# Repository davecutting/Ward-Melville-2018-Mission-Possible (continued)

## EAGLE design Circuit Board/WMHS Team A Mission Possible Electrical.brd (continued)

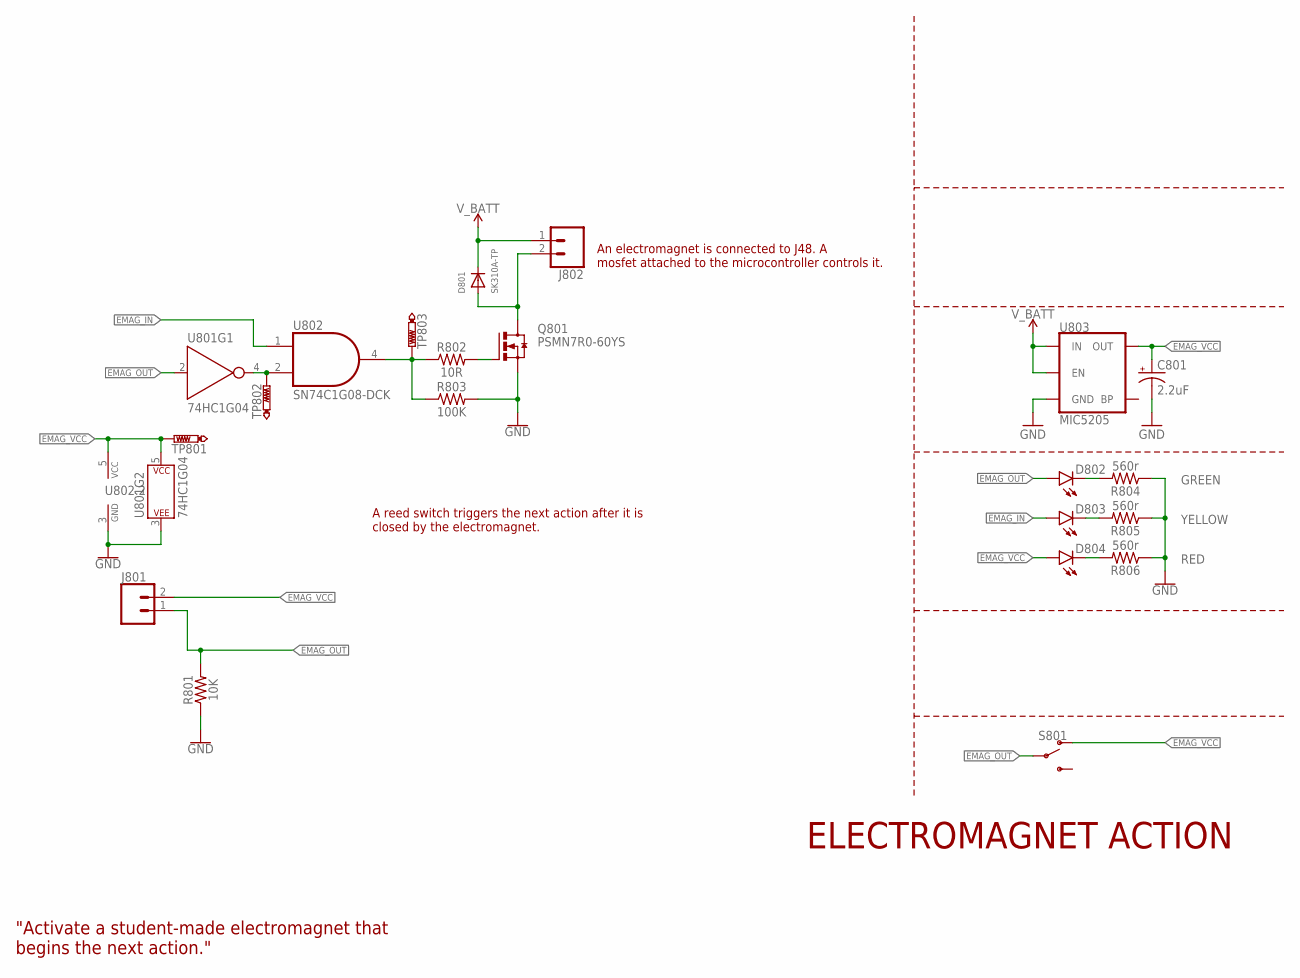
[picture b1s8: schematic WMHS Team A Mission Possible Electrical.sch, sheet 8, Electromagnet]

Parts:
C801: 2.2uF; EIA3216
D801: SK310A-TP; SMADIODE
D802: GREEN; LED-0603
D803: YELLOW; LED-0603
D804: RED; LED-0603
J801: CONN_02LOCK; 1X02_LOCK
J802: CONN_023.5MM_LOCK; SCREWTERMINAL-3.5MM-2_LOCK
Q801: PSMN7R0-60YS; SOT669
R801: 10K; 0603
R802: 10R; 0603
R803: 100K; 0603
R804, R805, R806: 560r; 0603
S801: SWITCH-SPDT-SMD-AYZ0202; SWITCH_DPDT_SMD_AYZ0202
TP801, TP802, TP803: PTR1TP20R; TP20R
U801: 74HC1G04; SOT353
U802: SN74C1G08-DCK; SC-70-5
U803: MIC5205; SOT23-5

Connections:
EMAG_IN: D803.A, U802.1 (A); also elsewhere on the board
EMAG_OUT: D802.A, J801.1, R801.2, S801.2, U801.2 (A); also elsewhere on the board
EMAG_VCC: C801.+, D804.A, J801.2, S801.1 (O), TP801.TP, U801.5 (P$V+), U802.5 (VCC), U803.5 (OUT)
GND: C801.-, Q801.1 (S), Q801.2 (S), Q801.3 (S), R801.1, R803.2, R804.1, R805.1, R806.1, U801.3 (P$V-), U802.3 (GND), U803.2 (GND); also elsewhere on the board
unnamed: TP802.TP, U801.4 (Y), U802.2 (B)
unnamed: R802.1, R803.1, TP803.TP, U802.4 (Y)
unnamed: Q801.4 (G), R802.2
unnamed: D801.A, J802.2, Q801.MB (D)
unnamed: D804.C, R806.2
unnamed: D803.C, R805.2
unnamed: D802.C, R804.2
V_BATT: D801.C, J802.1, U803.1 (IN), U803.3 (EN); also elsewhere on the board

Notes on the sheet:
ELECTROMAGNET ACTION
"Activate a student-made electromagnet that begins the next action."
An electromagnet is connected to J48. A mosfet attached to the microcontroller controls it.
A reed switch triggers the next action after it is closed by the electromagnet.

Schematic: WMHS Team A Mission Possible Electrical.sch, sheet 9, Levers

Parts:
C901: 0.1uF; 0603
C902: 2.2uF; EIA3216
D901: SK310A-TP; SMADIODE
D902: GREEN; LED-0603
D903: YELLOW; LED-0603
D904: RED; LED-0603
J901: CONN_02LOCK; 1X02_LOCK
J902: CONN_023.5MM_LOCK; SCREWTERMINAL-3.5MM-2_LOCK
J903: ICSP_HEADER; 2X3
Q901: PSMN7R0-60YS; SOT669
R901: 10R; 0603
R902: 100K; 0603
R903, R904: 10K; 0603
R905, R906, R907: 560r; 0603
S901: RST; TACTILE_SWITCH_SMD_5.2MM
S902: SWITCH-SPDT-SMD-AYZ0202; SWITCH_DPDT_SMD_AYZ0202
TP901, TP902: PTR1TP20R; TP20R
U901: ATTINY25-20SSUR; SOIC8
U902: MIC5205; SOT23-5

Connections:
GND: C901.1, C902.-, J903.6, Q901.1 (S), Q901.2 (S), Q901.3 (S), R902.2, R903.2, R905.1, R906.1, R907.1, S901.1, S901.2 (1), U901.4 (GND), U902.2 (GND); also elsewhere on the board
LEVER_IN: D903.A, U901.2 (PB3(ADC3)); also elsewhere on the board
LEVER_MISO: J903.1, U901.6 (PB1(MISO))
LEVER_MOSI: J903.4, U901.5 (PB0(MOSI))
LEVER_OUT: D902.A, J901.2, R903.1, S902.2; also elsewhere on the board
LEVER_RST: J903.5, R904.1, S901.3 (2), S901.4 (2), U901.1 (PB5(NRES))
LEVER_SCK: J903.3, R901.1, R902.1, U901.7 (PB2(SCK/ADC1))
LEVER_VCC: C901.2, C902.+, D904.A, J901.1, J903.2, R904.2, S902.1 (O), TP901.TP, U901.8 (VCC), U902.5 (OUT)
unnamed: TP902.TP, U901.3 (PB4(ADC2))
unnamed: Q901.4 (G), R901.2
unnamed: D901.A, J902.2, Q901.MB (D)
unnamed: D904.C, R907.2
unnamed: D903.C, R906.2
unnamed: D902.C, R905.2
V_BATT: D901.C, J902.1, U902.1 (IN), U902.3 (EN); also elsewhere on the board

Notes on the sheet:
LEVER ACTION
"Use the mechanical advantage of all 3 classes of levers in sequence to begin the next action."
A solenoid is connected to J50. A mosfet attached to the microcontroller controls it. After a short period of activation, the mosfet is turned off and the solenoid releases.
A normally open limit switch connected to J53 is pressed by the levers.
https://www.ebay.com/itm/DC12V-2A-20N-10mm-Pull-Push-Type-Linear-Motion-Solenoid-Electromagnet-/ 253056280056?_trksid=p2349526.m4383.l4275.c1

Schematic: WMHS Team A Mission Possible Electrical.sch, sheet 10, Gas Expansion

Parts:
C1001: 0.1uF; 0603
C1002: 2.2uF; EIA3216
D1001: SK310A-TP; SMADIODE
D1002: GREEN; LED-0603
D1003: YELLOW; LED-0603
D1004: RED; LED-0603
J1001: CONN_023.5MM_LOCK; SCREWTERMINAL-3.5MM-2_LOCK
J1002, J1003, J1004: CONN_02LOCK; 1X02_LOCK
J1005: ICSP_HEADER; 2X3
Q1001: PSMN7R0-60YS; SOT669
R1001: 10R; 0603
R1002, R1003: 100K; 0603
R1004: 1M; 0603
R1005: 10K; 0603
R1006, R1007, R1008: 560r; 0603
S1001: RST; TACTILE_SWITCH_SMD_5.2MM
S1002: SWITCH-SPDT-SMD-AYZ0202; SWITCH_DPDT_SMD_AYZ0202
TP1001, TP1002: PTR1TP20R; TP20R
U1001: ATTINY25-20SSUR; SOIC8
U1002: MIC5205; SOT23-5

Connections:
EXP_IN: D1003.A, U1001.2 (PB3(ADC3)); also elsewhere on the board
EXP_MISO: J1005.1, U1001.6 (PB1(MISO))
EXP_MOSI: J1005.4, R1001.1, R1002.1, U1001.5 (PB0(MOSI))
EXP_OUT: D1002.A, J1004.2, R1004.1, S1002.2; also elsewhere on the board
EXP_RST: J1005.5, R1005.1, S1001.3 (2), S1001.4 (2), U1001.1 (PB5(NRES))
EXP_SCK: J1005.3, R1003.2, U1001.7 (PB2(SCK/ADC1))
EXP_VCC: C1001.2, C1002.+, D1004.A, J1004.1, J1005.2, R1005.2, S1002.1 (O), TP1001.TP, U1001.8 (VCC), U1002.5 (OUT)
GND: C1001.1, C1002.-, J1002.2, J1003.2, J1005.6, Q1001.1 (S), Q1001.2 (S), Q1001.3 (S), R1002.2, R1004.2, R1006.1, R1007.1, R1008.1, S1001.1, S1001.2 (1), U1001.4 (GND), U1002.2 (GND); also elsewhere on the board
unnamed: Q1001.4 (G), R1001.2
unnamed: TP1002.TP, U1001.3 (PB4(ADC2))
unnamed: J1002.1, R1003.1
unnamed: D1001.A, J1001.2, Q1001.MB (D)
unnamed: D1004.C, R1008.2
unnamed: D1003.C, R1007.2
unnamed: D1002.C, R1006.2
V_BATT: D1001.C, J1001.1, J1003.1, U1002.1 (IN), U1002.3 (EN); also elsewhere on the board

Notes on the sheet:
GAS EXPANSION ACTION
"Use a thermal reaction which expands a gas to activate the next action." CLARIFICATION: "Use a change in temperature which expands a gas to activate the next action."
12V 40W ceramic cartridge heater is connected to J38. A mosfet attached to the microcontroller controls the heater.
A normally open limit switch connected to J1 is pressed by the expanding gas pushing on and displacing the syringe plunger.
A thermistor connected to J39 provides feedback for the heater cartridge and is used in the PID loop.
An optional 12V brushless fan can be connected to J5 in order to cool the interface between the heater and the device

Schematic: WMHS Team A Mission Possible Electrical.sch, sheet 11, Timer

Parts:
C1101, C1103: 0.1uF; 0603
C1102: 0.33uF; 0603
D1101: GREEN; LED-0603
D1102: YELLOW; LED-0603
D1103: RED; LED-0603
IC1101: 7805DT; TO252
J1101, J1102, J1103: CONN_02LOCK; 1X02_LOCK
J1104: ICSP_HEADER; 2X3
R1101, R1102, R1103: 10K; 0603
R1104, R1105, R1106: 560r; 0603
S1101: RST; TACTILE_SWITCH_SMD_5.2MM
S1102: SWITCH-SPDT-SMD-AYZ0202; SWITCH_DPDT_SMD_AYZ0202
TP1101, TP1102: PTR1TP20R; TP20R
U1101: DRV8835; WSON-12
U1102: ATTINY25-20SSUR; SOIC8

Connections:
GND: C1101.1, C1102.1, C1103.2, IC1101.3 (GND), J1104.6, R1101.2, R1102.2, R1104.1, R1105.1, R1106.1, S1101.1, S1101.2 (1), U1101.6 (VSS), U1101.PAD (VSS), U1102.4 (GND); also elsewhere on the board
unnamed: TP1102.TP, U1102.3 (PB4(ADC2))
unnamed: J1102.1, U1101.2 (AOUT1)
unnamed: J1102.2, U1101.3 (AOUT2)
unnamed: D1103.C, R1106.2
unnamed: D1102.C, R1105.2
unnamed: D1101.C, R1104.2
TIMER_IN: D1102.A, U1102.2 (PB3(ADC3)); also elsewhere on the board
TIMER_MISO: J1104.1, U1101.9 (AIN2/EN), U1102.6 (PB1(MISO))
TIMER_MOSI: J1104.4, U1101.10 (AIN1/PH), U1102.5 (PB0(MOSI))
TIMER_OUT: D1101.A, J1101.2, R1101.1, S1102.2; also elsewhere on the board
TIMER_RST: J1104.5, R1103.1, S1101.3 (2), S1101.4 (2), U1102.1 (PB5(NRES))
TIMER_SCK: J1103.2, J1104.3, R1102.1, U1102.7 (PB2(SCK/ADC1))
TIMER_VCC: C1101.2, C1103.1, D1103.A, IC1101.2 (VO), J1101.1, J1103.1, J1104.2, R1103.2, S1102.1 (O), TP1101.TP, U1101.1 (VM), U1101.11 (MODE), U1101.12 (VCC), U1102.8 (VCC)
V_BATT: C1102.2, IC1101.1 (VI); also elsewhere on the board

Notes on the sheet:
CHEMICAL TIMER
"To receive Bonus Points, participants must designate an action, either scorable or non- scorable, taking over 30 seconds that does not use electricity or springs for power."
A normally open limit switch connected to J55 is pressed by the expanding gas.
A motor connected to J54 flips the pressure chamber then pulses back and forth for several seconds to ensure the alkaseltzer is mixing with the water.
A normally open limit switch tells the motor driver when to shut off.

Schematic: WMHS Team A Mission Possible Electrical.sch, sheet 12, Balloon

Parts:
C1201, C1203: 0.1uF; 0603
C1202: 0.33uF; 0603
D1201: GREEN; LED-0603
D1202: YELLOW; LED-0603
D1203: RED; LED-0603
IC1201: 7805DT; TO252
J1201, J1202, J1203: CONN_02LOCK; 1X02_LOCK
J1204: ICSP_HEADER; 2X3
R1201, R1202, R1203: 10K; 0603
R1204, R1205, R1206: 560r; 0603
S1201: RST; TACTILE_SWITCH_SMD_5.2MM
S1202: SWITCH-SPDT-SMD-AYZ0202; SWITCH_DPDT_SMD_AYZ0202
TP1201, TP1202: PTR1TP20R; TP20R
U1201: DRV8835; WSON-12
U1202: ATTINY25-20SSUR; SOIC8

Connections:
BALLOON_IN: D1202.A, U1202.2 (PB3(ADC3)); also elsewhere on the board
BALLOON_MISO: J1204.1, U1201.9 (AIN2/EN), U1202.6 (PB1(MISO))
BALLOON_MOSI: J1204.4, U1201.10 (AIN1/PH), U1202.5 (PB0(MOSI))
BALLOON_OUT: D1201.A, J1201.2, R1201.1, S1202.2; also elsewhere on the board
BALLOON_RST: J1204.5, R1203.1, S1201.3 (2), S1201.4 (2), U1202.1 (PB5(NRES))
BALLOON_SCK: J1202.2, J1204.3, R1202.1, U1202.7 (PB2(SCK/ADC1))
BALLOON_VCC: C1201.2, C1203.1, D1203.A, IC1201.2 (VO), J1201.1, J1202.1, J1204.2, R1203.2, S1202.1 (O), TP1201.TP, U1201.1 (VM), U1201.11 (MODE), U1201.12 (VCC), U1202.8 (VCC)
GND: C1201.1, C1202.1, C1203.2, IC1201.3 (GND), J1204.6, R1201.2, R1202.2, R1204.1, R1205.1, R1206.1, S1201.1, S1201.2 (1), U1201.6 (VSS), U1201.PAD (VSS), U1202.4 (GND); also elsewhere on the board
unnamed: TP1202.TP, U1202.3 (PB4(ADC2))
unnamed: J1203.1, U1201.2 (AOUT1)
unnamed: J1203.2, U1201.3 (AOUT2)
unnamed: D1203.C, R1206.2
unnamed: D1202.C, R1205.2
unnamed: D1201.C, R1204.2
V_BATT: C1202.2, IC1201.1 (VI); also elsewhere on the board

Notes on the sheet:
BALLOON ACTION
"Use a chemical reaction that inflates a balloon so that the balloon strikes an object that originally was at least 20 cm away from the balloon, so that the action of striking the object continues the sequence of events."
A normally open limit switch connected to J7 is pressed by the expanding balloon.
A motor connected to J40 flips the pressure chamber then pulses back and forth to mix the fluids.
A normally open limit switch tells the motor driver when to shut off.

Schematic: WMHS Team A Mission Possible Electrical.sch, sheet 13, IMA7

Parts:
C1301, C1303: 0.1uF; 0603
C1302: 0.33uF; 0603
D1301: GREEN; LED-0603
D1302: YELLOW; LED-0603
D1303: RED; LED-0603
IC1301: 7805DT; TO252
J1301, J1302, J1303: CONN_02LOCK; 1X02_LOCK
J1304: ICSP_HEADER; 2X3
R1301, R1302, R1303: 10K; 0603
R1304, R1305, R1306: 560r; 0603
S1301: RST; TACTILE_SWITCH_SMD_5.2MM
S1302: SWITCH-SPDT-SMD-AYZ0202; SWITCH_DPDT_SMD_AYZ0202
TP1301, TP1302: PTR1TP20R; TP20R
U1301: DRV8835; WSON-12
U1302: ATTINY25-20SSUR; SOIC8

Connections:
GND: C1301.1, C1302.1, C1303.2, IC1301.3 (GND), J1304.6, R1301.2, R1302.2, R1304.1, R1305.1, R1306.1, S1301.1, S1301.2 (1), U1301.6 (VSS), U1301.PAD (VSS), U1302.4 (GND); also elsewhere on the board
IMA7_IN: D1302.A, U1302.2 (PB3(ADC3)); also elsewhere on the board
IMA7_MISO: J1304.1, U1301.9 (AIN2/EN), U1302.6 (PB1(MISO))
IMA7_MOSI: J1304.4, U1301.10 (AIN1/PH), U1302.5 (PB0(MOSI))
IMA7_OUT: D1301.A, J1301.2, R1301.1, S1302.2; also elsewhere on the board
IMA7_RST: J1304.5, R1303.1, S1301.3 (2), S1301.4 (2), U1302.1 (PB5(NRES))
IMA7_SCK: J1302.2, J1304.3, R1302.1, U1302.7 (PB2(SCK/ADC1))
IMA7_VCC: C1301.2, C1303.1, D1303.A, IC1301.2 (VO), J1301.1, J1302.1, J1304.2, R1303.2, S1302.1 (O), TP1301.TP, U1301.1 (VM), U1301.11 (MODE), U1301.12 (VCC), U1302.8 (VCC)
unnamed: TP1302.TP, U1302.3 (PB4(ADC2))
unnamed: J1303.1, U1301.2 (AOUT1)
unnamed: J1303.2, U1301.3 (AOUT2)
unnamed: D1303.C, R1306.2
unnamed: D1302.C, R1305.2
unnamed: D1301.C, R1304.2
V_BATT: C1302.2, IC1301.1 (VI); also elsewhere on the board

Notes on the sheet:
IMA 7 PULLEY ACTION
"Use a Pulley system with an ideal mechanical advantage (IMA) of at least 7, that lifts an object that is at least 500 g at least 10 vertical cm before the object initiates the next action."
A normally open limit switch connected to J42 is pressed by the mass as it lifts
A motor connected to J41 rotates, pulling the string that is connected to the mass
A normally closed limit switch connected to this header is pressed by the mass as it raises

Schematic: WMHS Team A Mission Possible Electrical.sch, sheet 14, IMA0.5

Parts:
C1401: 2.2uF; EIA3216
D1401: SK310A-TP; SMADIODE
D1402: GREEN; LED-0603
D1403: YELLOW; LED-0603
D1404: RED; LED-0603
J1401: CONN_02LOCK; 1X02_LOCK
J1402: CONN_023.5MM_LOCK; SCREWTERMINAL-3.5MM-2_LOCK
JP1401: JUMPER-SMT_2_NO_SILK; SMT-JUMPER_2_NO_SILK
JP1402: JUMPER-SMT_2_NC_TRACE_SILK; SMT-JUMPER_2_NC_TRACE_SILK
Q1401: PSMN7R0-60YS; SOT669
R1401: 10K; 0603
R1402: 10R; 0603
R1403: 100K; 0603
R1404, R1405, R1406: 560r; 0603
S1401: SWITCH-SPDT-SMD-AYZ0202; SWITCH_DPDT_SMD_AYZ0202
TP1401, TP1402: PTR1TP20R; TP20R
U1401: 74HC1G04; SOT353
U1402: MIC5205; SOT23-5

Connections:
GND: C1401.-, Q1401.1 (S), Q1401.2 (S), Q1401.3 (S), R1401.2, R1403.2, R1404.1, R1405.1, R1406.1, U1401.3 (P$V-), U1402.2 (GND); also elsewhere on the board
IMA0.5_IN: D1403.A, JP1401.1, U1401.2 (A); also elsewhere on the board
IMA0.5_OUT: D1402.A, J1401.2, R1401.1, S1401.2; also elsewhere on the board
IMA0.5_VCC: C1401.+, D1404.A, J1401.1, S1401.1 (O), TP1402.TP, U1401.5 (P$V+), U1402.5 (OUT)
unnamed: JP1401.2, JP1402.2, R1402.1, R1403.1, TP1401.TP
unnamed: JP1402.1, U1401.4 (Y)
unnamed: Q1401.4 (G), R1402.2
unnamed: D1401.A, J1402.2, Q1401.MB (D)
unnamed: D1404.C, R1406.2
unnamed: D1403.C, R1405.2
unnamed: D1402.C, R1404.2
V_BATT: D1401.C, J1402.1, U1402.1 (IN), U1402.3 (EN); also elsewhere on the board

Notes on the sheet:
IMA 0.5 PULLEY ACTION
"Use a Pulley system that has an ideal mechanical advantage (IMA) of 0.50 that lifts an object that is at least 500 g at least 10 vertical cm before the object initiates the next action."
An electromagnet is connected to this header. The electromagnet deactivates, dropping a conterweight.
A normally open limit switch connected to this header is pressed by the mass as it raises
https://www.amazon.com/uxcell-Electric-Lifting-Electromagnet-Solenoid/dp/B01N3387AA/ref=sr_1_4?ie=UTF8&qid=1513817515&sr=8-4&keywords=electromagnet&th=1

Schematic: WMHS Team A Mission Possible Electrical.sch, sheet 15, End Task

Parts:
C1501: 0.33uF; 0603
C1502: 0.1uF; 0603
D1501: YELLOW; LED-0603
D1502: RED; LED-0603
IC1501: 7805DT; TO252
J1501: CONN_03LOCK; 1X03_LOCK
R1501: 10K; 0603
R1502, R1503: 560r; 0603
TP1501: PTR1TP20R; TP20R

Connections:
END_IN: D1501.A, J1501.1, R1501.2; also elsewhere on the board
END_VCC: C1502.1, D1502.A, IC1501.2 (VO), J1501.2, TP1501.TP
GND: C1501.1, C1502.2, IC1501.3 (GND), J1501.3, R1501.1, R1502.1, R1503.1; also elsewhere on the board
unnamed: D1502.C, R1503.2
unnamed: D1501.C, R1502.2
V_BATT: C1501.2, IC1501.1 (VI); also elsewhere on the board

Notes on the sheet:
END TASK
"The device must play a recording of the phrase “The End” to signal the end of the run. This phrase must be clearly audible, and demonstrated for the judges prior to the run."
Previous transfer triggers sound recoring module (connected to J6), which then plays the end recording.

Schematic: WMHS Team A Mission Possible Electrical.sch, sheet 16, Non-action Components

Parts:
C1601, C1602, C1603: 100uF; PANASONIC_D
C1604: 0.1uF; 0603
D1601: SMAJ30A; SMADIODE
J1601, J1602, J1603, J1604, J1605, J1606, J1607, J1608, J1609, J1610, J1611, J1612, J1613, J1614: CONN_02; 1X02
X1601: MSTBA2

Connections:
BALLOON_IN: J1611.1; also elsewhere on the board
BALLOON_OUT: J1612.2; also elsewhere on the board
COIN_IN: J1601.1; also elsewhere on the board
COIN_OUT: J1602.2; also elsewhere on the board
EMAG_IN: J1607.1; also elsewhere on the board
EMAG_OUT: J1608.2; also elsewhere on the board
ENDO_IN: J1604.1; also elsewhere on the board
ENDO_OUT: J1605.2; also elsewhere on the board
END_IN: J1614.1; also elsewhere on the board
EXO_IN: J1602.1; also elsewhere on the board
EXO_OUT: J1603.2; also elsewhere on the board
EXP_IN: J1609.1; also elsewhere on the board
EXP_OUT: J1610.2; also elsewhere on the board
GND: C1601.-, C1602.-, C1603.-, C1604.2, D1601.A, X1601.2; also elsewhere on the board
IMA0.5_IN: J1613.1; also elsewhere on the board
IMA0.5_OUT: J1614.2; also elsewhere on the board
IMA7_IN: J1612.1; also elsewhere on the board
IMA7_OUT: J1613.2; also elsewhere on the board
IR_IN: J1606.1; also elsewhere on the board
IR_OUT: J1607.2; also elsewhere on the board
LEVER_IN: J1608.1; also elsewhere on the board
LEVER_OUT: J1609.2; also elsewhere on the board
LIGHT_IN: J1603.1; also elsewhere on the board
LIGHT_OUT: J1604.2; also elsewhere on the board
START_OUT: J1601.2; also elsewhere on the board
TIMER_IN: J1610.1; also elsewhere on the board
TIMER_OUT: J1611.2; also elsewhere on the board
V_BATT: C1601.+, C1602.+, C1603.+, C1604.1, D1601.C, X1601.1; also elsewhere on the board
WATER_IN: J1605.1; also elsewhere on the board
WATER_OUT: J1606.2; also elsewhere on the board

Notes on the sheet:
Non-action Components

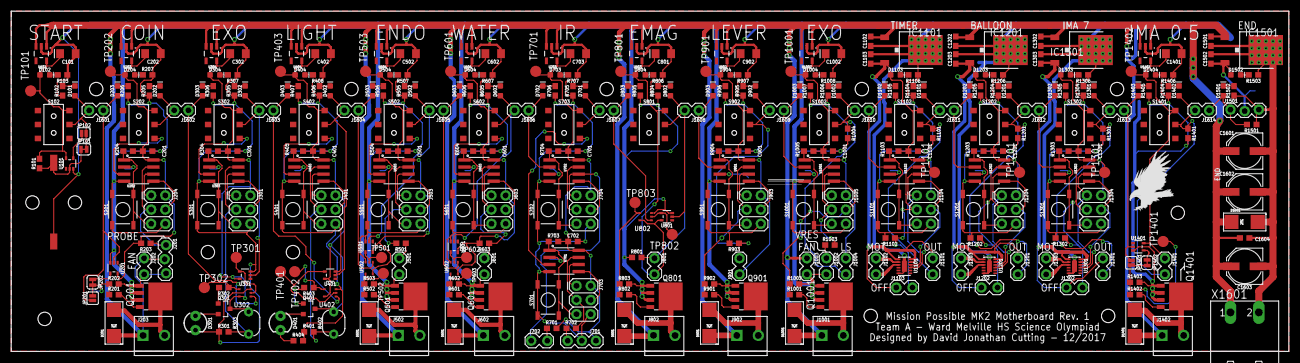
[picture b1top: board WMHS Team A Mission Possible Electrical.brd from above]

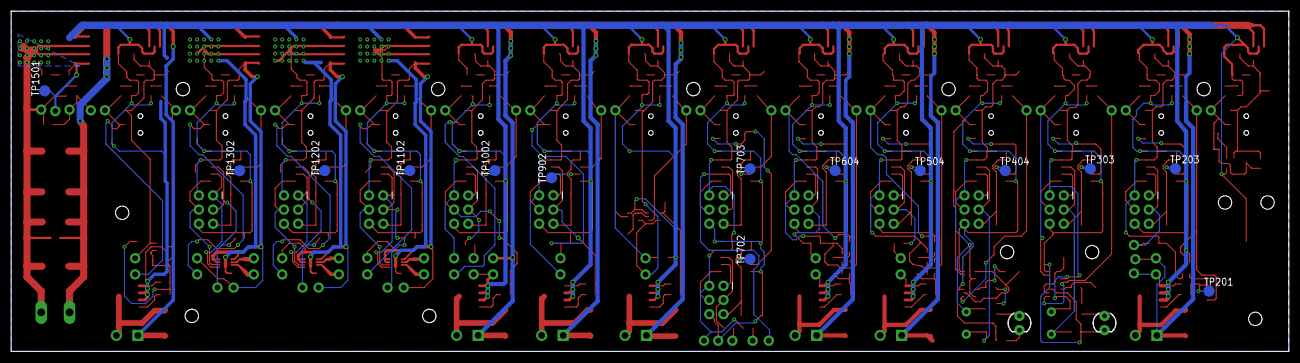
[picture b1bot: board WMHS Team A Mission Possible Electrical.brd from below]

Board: 2 copper layers, 228.9 x 60.9 mm, 362 parts (14 on the bottom side), 199 nets.

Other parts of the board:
U$2: EAGLE-PLC-8MM

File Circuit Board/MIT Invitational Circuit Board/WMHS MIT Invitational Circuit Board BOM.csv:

"Qty";"Value";"Device";"Package";"Parts";"Description";"";
"14";"";"CONN_02";"1X02";"J1601, J1602, J1603, J1604, J1605, J1606, J1607, J1608, J1609, J1610, J1611, J1612, J1613, J1614";"Multi connection point. Often used as Generic Header-pin footprint for 0.1 inch spaced/style header connections";"";
"7";"";"CONN_023.5MM_LOCK";"SCREWTERMINAL-3.5MM-2_LOCK";"J203, J502, J602, J802, J902, J1001, J1402";"Multi connection point. Often used as Generic Header-pin footprint for 0.1 inch spaced/style header connections";"";
"19";"";"CONN_02LOCK";"1X02_LOCK";"J202, J501, J601, J702, J801, J901, J1002, J1003, J1004, J1101, J1102, J1103, J1201, J1202, J1203, J1301, J1302, J1303, J1401";"Multi connection point. Often used as Generic Header-pin footprint for 0.1 inch spaced/style header connections";"";
"1";"";"CONN_03";"1X03";"J701";"Multi connection point. Often used as Generic Header-pin footprint for 0.1 inch spaced/style header connections";"";
"2";"";"CONN_03LOCK";"1X03_LOCK";"J201, J1501";"Multi connection point. Often used as Generic Header-pin footprint for 0.1 inch spaced/style header connections";"";
"14";"";"SWITCH-SPDT-SMD-AYZ0202";"SWITCH_DPDT_SMD_AYZ0202";"S102, S202, S302, S402, S502, S602, S703, S801, S902, S1002, S1102, S1202, S1302, S1401";"Single Pole, Double Throw (SPDT) Switch";"";
"1";"0.1uF";"0.1UF-0603-100V-10%";"0603";"C1103";"0.1µF ceramic capacitors";"";
"3";"0.1uF";"0.1UF-0603-25V-(+80/-20%)";"0603";"C1203, C1303, C1502";"0.1µF ceramic capacitors";"";
"13";"0.1uF";"0.1UF-0603-25V-5%";"0603";"C201, C301, C401, C501, C601, C701, C702, C901, C1001, C1101, C1201, C1301, C1604";"0.1µF ceramic capacitors";"";
"4";"0.33uF";"0.1UF-0603-25V-(+80/-20%)";"0603";"C1102, C1202, C1302, C1501";"0.1µF ceramic capacitors";"";
"9";"100K";"RESISTOR0603";"0603";"R202, R501, R503, R602, R803, R902, R1002, R1003, R1403";"Generic Resistor Package";"";
"3";"100uF";"100UF-POLAR-25V-20%(ELEC)";"PANASONIC_D";"C1601, C1602, C1603";"100µF polarized capacitors";"";
"13";"10K";"330OHM-0603-1/10W-1%";"0603";"R101, R204, R304, R405, R504, R604, R703, R704, R904, R1005, R1103, R1203, R1303";"330O resistor";"";
"13";"10K";"RESISTOR0603";"0603";"R301, R401, R801, R903, R1004, R1101, R1102, R1201, R1202, R1301, R1302, R1401, R1501";"Generic Resistor Package";"";
"7";"10R";"RESISTOR0603";"0603";"R201, R502, R601, R802, R901, R1001, R1402";"Generic Resistor Package";"";
"1";"10k";"RESISTOR0603";"0603";"R203";"Generic Resistor Package";"";
"2";"1K";"RESISTOR0603";"0603";"R302, R403";"Generic Resistor Package";"";
"1";"1M";"RESISTOR0603";"0603";"R603";"Generic Resistor Package";"";
"11";"2.2uF";"10UF-POLAR-EIA3216-16V-10%(TANT)";"EIA3216";"C101, C202, C302, C402, C502, C602, C703, C801, C902, C1002, C1401";"10.0µF polarized capacitors";"";
"1";"330r";"RESISTOR0603";"0603";"R701";"Generic Resistor Package";"";
"1";"33k";"RESISTOR0603";"0603";"R702";"Generic Resistor Package";"";
"2";"500mA/300V";"TRANS_NPN-MMBTA42";"SOT23-3";"Q301, Q401";"NPN transistor";"";
"1";"560";"RESISTOR0603";"0603";"R404";"Generic Resistor Package";"";
"43";"560r";"330OHM-0603-1/10W-1%";"0603";"R102, R103, R205, R206, R207, R305, R306, R307, R406, R407, R408, R505, R506, R507, R605, R606, R607, R705, R706, R707, R804, R805, R806, R905, R906, R907, R1006, R1007, R1008, R1104, R1105, R1106, R1204, R1205, R1206, R1304, R1305, R1306, R1404, R1405, R1406, R1502, R1503";"330O resistor";"";
"8";"74HC1G04";"74HC1G04";"SOT353";"U101, U201, U301, U401, U501, U601, U801, U1401";"Single Inverter";"";
"4";"7805DT";"7805DT";"TO252";"IC1101, IC1201, IC1301, IC1501";"Positive VOLTAGE REGULATOR";"";
"12";"ATTINY25-20SSUR";"ATTINY45-SMT-NARROW";"SOIC8";"U202, U303, U403, U503, U603, U701, U702, U901, U1001, U1102, U1202, U1302";"Atmel 8-pin 2/4/8kB flash uC";"";
"3";"DRV8835";"DRV883X";"WSON-12";"U1101, U1201, U1301";"DRV8835 2 Channel Motor Driver";"";
"14";"GREEN";"LED-GREEN0603";"LED-0603";"D101, D202, D302, D402, D502, D602, D701, D802, D902, D1002, D1101, D1201, D1301, D1402";"Green SMD LED";"";
"12";"ICSP_HEADER";"AVR_SPI_PROG_3X2PTH";"2X3";"J204, J301, J401, J503, J603, J703, J704, J903, J1005, J1104, J1204, J1304";"AVR ISP 6 Pin";"";
"1";"INCANDESCENT";"LED3MM";"LED_3MM";"D301";"LED (Generic)";"";
"2";"JUMPER-SMT_2_NC_TRACE_SILK";"JUMPER-SMT_2_NC_TRACE_SILK";"SMT-JUMPER_2_NC_TRACE_SILK";"JP202, JP1402";"Normally closed trace jumper";"";
"3";"JUMPER-SMT_2_NO_SILK";"JUMPER-SMT_2_NO_SILK";"SMT-JUMPER_2_NO_SILK";"JP102, JP201, JP1401";"Normally open jumper";"";
"1";"JUMPER_NC_TRACE";"JUMPER-SMT_2_NC_TRACE_SILK";"SMT-JUMPER_2_NC_TRACE_SILK";"JP101";"Normally closed trace jumper";"";
"11";"MIC5205";"V_REG_MIC52055V";"SOT23-5";"U102, U203, U304, U404, U504, U604, U703, U803, U902, U1002, U1402";"V_REG MIC5205 Standard 3.3V, 5V, and Adjustable 150mA LDO voltage regulator in SOT-23 layout. Micrel part MIC5205. BP (by-pass) pin is used to lower output noise with 470pF cap, may be left open. On the adjustable version BP is used to set output.";"";
"1";"MSTBA2";"MSTBA2";"MSTBA2";"X1601";"PHOENIX";"";
"2";"PHOTOCELLPTH";"PHOTOCELLPTH";"PHOTOCELL";"R303, R402";"Photocell (Photodetector, Photo Resistor, CdS)";"";
"7";"PSMN7R0-60YS";"PSMN7R0-60YS";"SOT669";"Q201, Q501, Q601, Q801, Q901, Q1001, Q1401";"";"";
"38";"PTR1TP20R";"PTR1TP20R";"TP20R";"TP101, TP201, TP202, TP203, TP301, TP302, TP303, TP401, TP402, TP403, TP404, TP501, TP502, TP503, TP504, TP601, TP602, TP603, TP604, TP701, TP702, TP703, TP801, TP802, TP803, TP901, TP902, TP1001, TP1002, TP1101, TP1102, TP1201, TP1202, TP1301, TP1302, TP1401, TP1402, TP1501";"TEST PIN";"";
"15";"RED";"LED-RED0603";"LED-0603";"D102, D204, D304, D404, D504, D604, D703, D804, D904, D1004, D1103, D1203, D1303, D1404, D1502";"Red SMD LED";"";
"1";"REED_SWITCH";"MDSM-10_REED_SWITCH";"AXIAL_GULLWING_REED";"S101";"";"";
"12";"RST";"MOMENTARY-SWITCH-SPST-SMD-5.2-REDUNDANT";"TACTILE_SWITCH_SMD_5.2MM";"S201, S301, S401, S501, S601, S701, S702, S901, S1001, S1101, S1201, S1301";"Momentary Switch (Pushbutton) - SPST";"";
"7";"SK310A-TP";"DIODESMA";"SMADIODE";"D201, D501, D601, D801, D901, D1001, D1401";"Diode";"";
"1";"SMAJ30A";"DIODESMA";"SMADIODE";"D1601";"Diode";"";
"5";"SN74*C1G08-DCK";"SN74*C1G08-DCK";"SC-70-5";"U302, U402, U502, U602, U802";"Ti's SN74AHC1G08 is a single 2-input positive-AND gate";"";
"1";"WHITE";"LED3MM";"LED_3MM";"D401";"LED (Generic)";"";
"14";"YELLOW";"LED-YELLOW0603";"LED-0603";"D203, D303, D403, D503, D603, D702, D803, D903, D1003, D1102, D1202, D1302, D1403, D1501";"Yellow SMD LED";"";

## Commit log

2018-01-15 Added beta circuit board design files
2018-01-22 Added code
2018-01-22 Reorganized files and updated schematics
    MIT schematics have been finalized and the code is pretty stable, beisdes some thresholding issues.
2018-01-22 Updated README.md and added PDF schematics and layouts
2018-01-22 Updated code version and schematics for regionals (beta version)
2018-01-22 Fixed readme extension
2018-01-22 Added overall readme, modified regionals readme.
2018-01-23 Changed file naming system
2018-03-03 SOUP and States Upgrades and Modifications
